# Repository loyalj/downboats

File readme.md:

A really basic board for adding and subtracting some numbers.  It usese touch sensing to interact with the user.

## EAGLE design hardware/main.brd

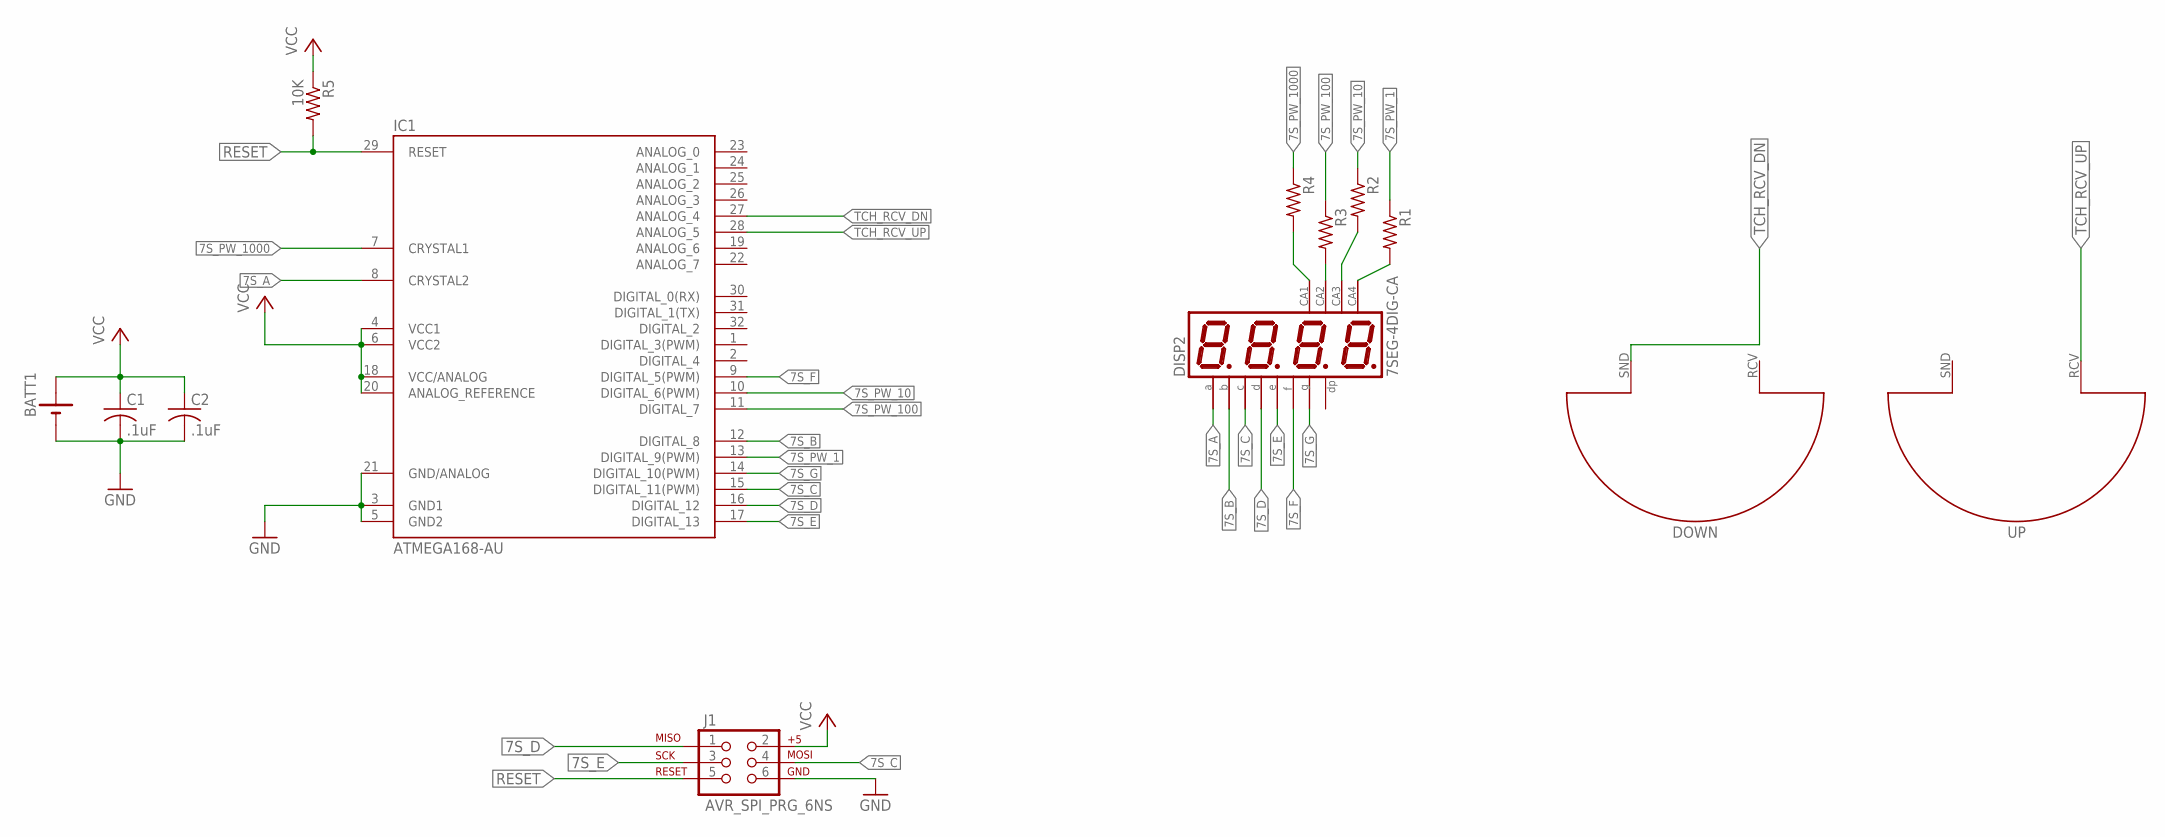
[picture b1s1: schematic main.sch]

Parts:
BATT1: 2032SMD
C1, C2: .1uF; C0603
DISP2: 7SEG-4DIG-CA; 7SEG-0.36-4
DOWN: AVD-TCH-01
IC1: ATMEGA168-AU; TQFP32-08
J1: AVR_SPI_PRG_6NS; 2X3-NS
R1, R2, R3, R4: R-US_R0603; R0603
R5: 10K; R0603
UP: AVD-TCH-01

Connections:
7S_A: DISP2.11 (A), IC1.8 (CRYSTAL2)
7S_B: DISP2.7 (B), IC1.12 (DIGITAL_8)
7S_C: DISP2.4 (C), IC1.15 (DIGITAL_11(PWM)), J1.4
7S_D: DISP2.2 (D), IC1.16 (DIGITAL_12), J1.1
7S_E: DISP2.1 (E), IC1.17 (DIGITAL_13), J1.3
7S_F: DISP2.10 (F), IC1.9 (DIGITAL_5(PWM))
7S_G: DISP2.5 (G), IC1.14 (DIGITAL_10(PWM))
7S_PW_1: IC1.13 (DIGITAL_9(PWM)), R1.1
7S_PW_10: IC1.10 (DIGITAL_6(PWM)), R2.1
7S_PW_100: IC1.11 (DIGITAL_7), R3.1
7S_PW_1000: IC1.7 (CRYSTAL1), R4.1
GND: BATT1.-, C1.2, C2.2, IC1.3 (GND1), IC1.5 (GND2), IC1.21 (GND/ANALOG), J1.6
unnamed: DISP2.6 (CA4), R1.2
unnamed: DISP2.8 (CA3), R2.2
unnamed: DISP2.9 (CA2), R3.2
unnamed: DISP2.12 (CA1), R4.2
RESET: IC1.29 (RESET), J1.5, R5.2
TCH_RCV_DN: DOWN.SND, IC1.27 (ANALOG_4)
TCH_RCV_UP: IC1.28 (ANALOG_5), UP.RCV
VCC: BATT1.+, C1.1, C2.1, IC1.4 (VCC1), IC1.6 (VCC2), IC1.18 (VCC/ANALOG), IC1.20 (ANALOG_REFERENCE), J1.2, R5.1

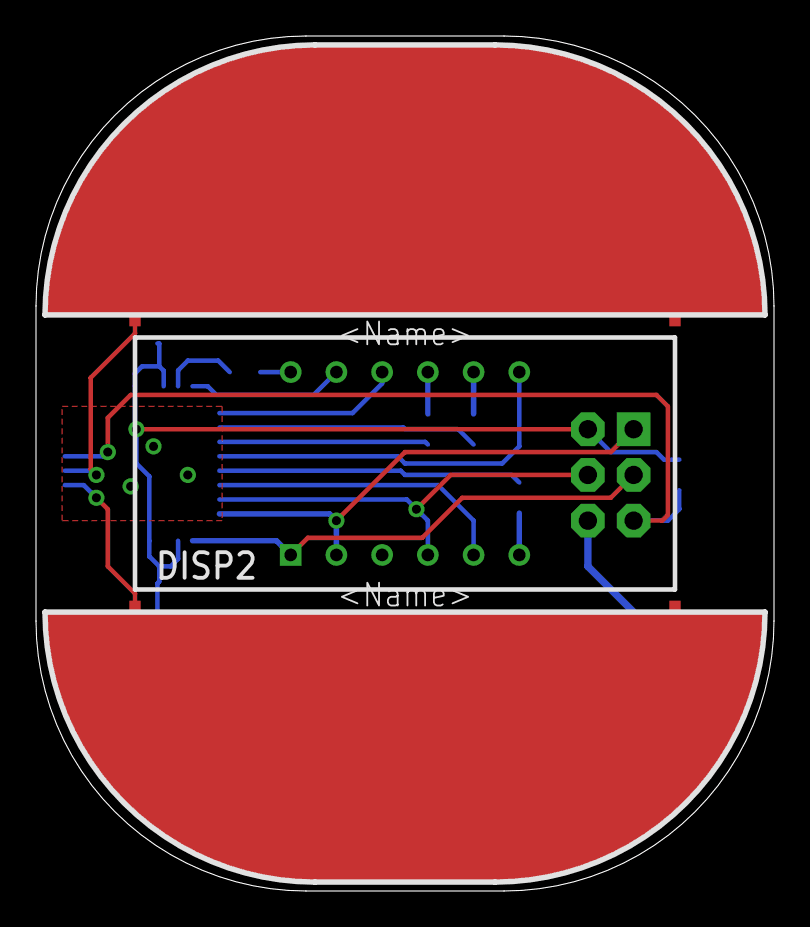
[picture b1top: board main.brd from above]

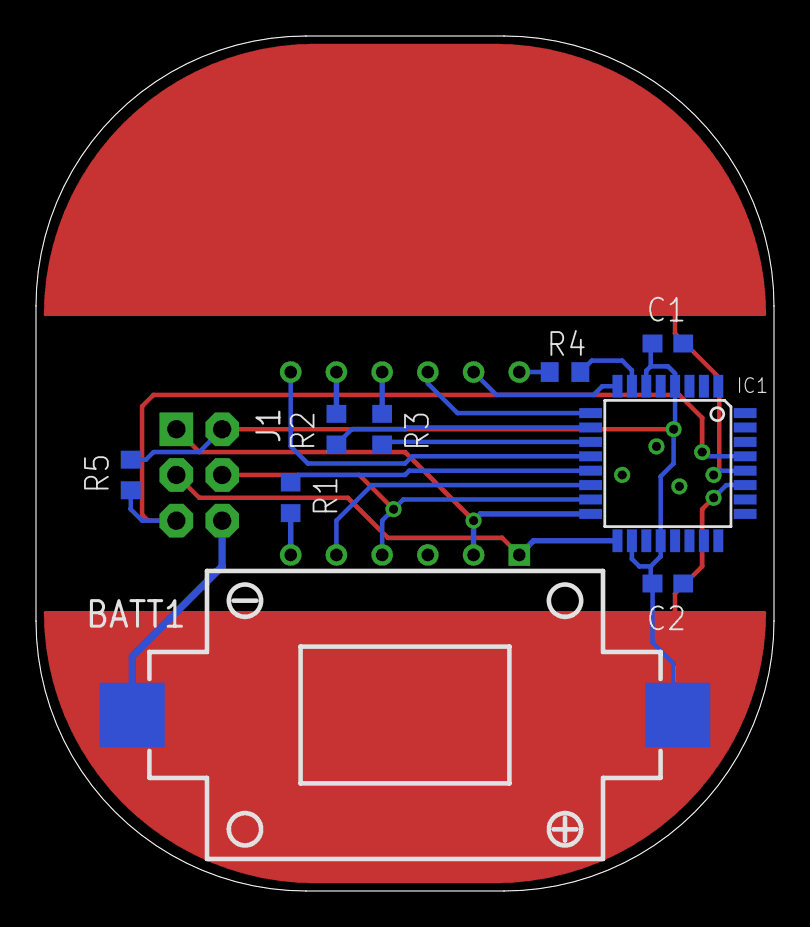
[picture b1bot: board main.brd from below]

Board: 2 copper layers, 41.0 x 47.5 mm, 13 parts (10 on the bottom side), 20 nets.

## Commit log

2014-10-09 initial commit of the downboats codez
2014-10-09 restructured repo
    better setup for holding software and hardware based data
2014-10-10 Adding schematic and layout, along with Gerber and Excellon files for manufacturing.
2014-10-10 HARDWARE MISTAKE: Did not include connection to Reset line. This makes the AVR unprogrammable without a jumper wire. Fixed.
2015-01-14 Some changes to the hardware design
2017-01-10 Hardware updates: 1. Changed display connection for cleaner layout 2. Changed touch sensor configuration for CVD touch sensing, and simpler layout 3. Changed passives to 0603 to ensmallen the board 4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
2017-01-10 Fixed error in schematic preventing back-annotation Fixed crossing traces in PCB Updated manufacturing data

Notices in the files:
parts and their libraries:
SparkFun-Connectors: Licensing: Creative Commons ShareAlike 4.0 International - https://creativecommons.org/licenses/by-sa/4.0
